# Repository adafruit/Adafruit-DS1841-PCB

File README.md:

## Adafruit DS1841 I2C Logarithmic Potentiometer PCB

<a href="http://www.adafruit.com/products/4570"><br/>
Click here to purchase one from the Adafruit shop</a>

PCB files for the Adafruit DS1841 I2C Logarithmic Potentiometer. 

Format is EagleCAD schematic and board layout
* https://www.adafruit.com/product/4570

### Description

INSERT PRODUCT COPY HERE

### License

Adafruit invests time and resources providing this open source design, please support Adafruit and open-source hardware by purchasing products from [Adafruit](https://www.adafruit.com)!

Designed by Limor Fried for Adafruit Industries.

Creative Commons Attribution/Share-Alike, all text above must be included in any redistribution. 
See license.txt for additional details.

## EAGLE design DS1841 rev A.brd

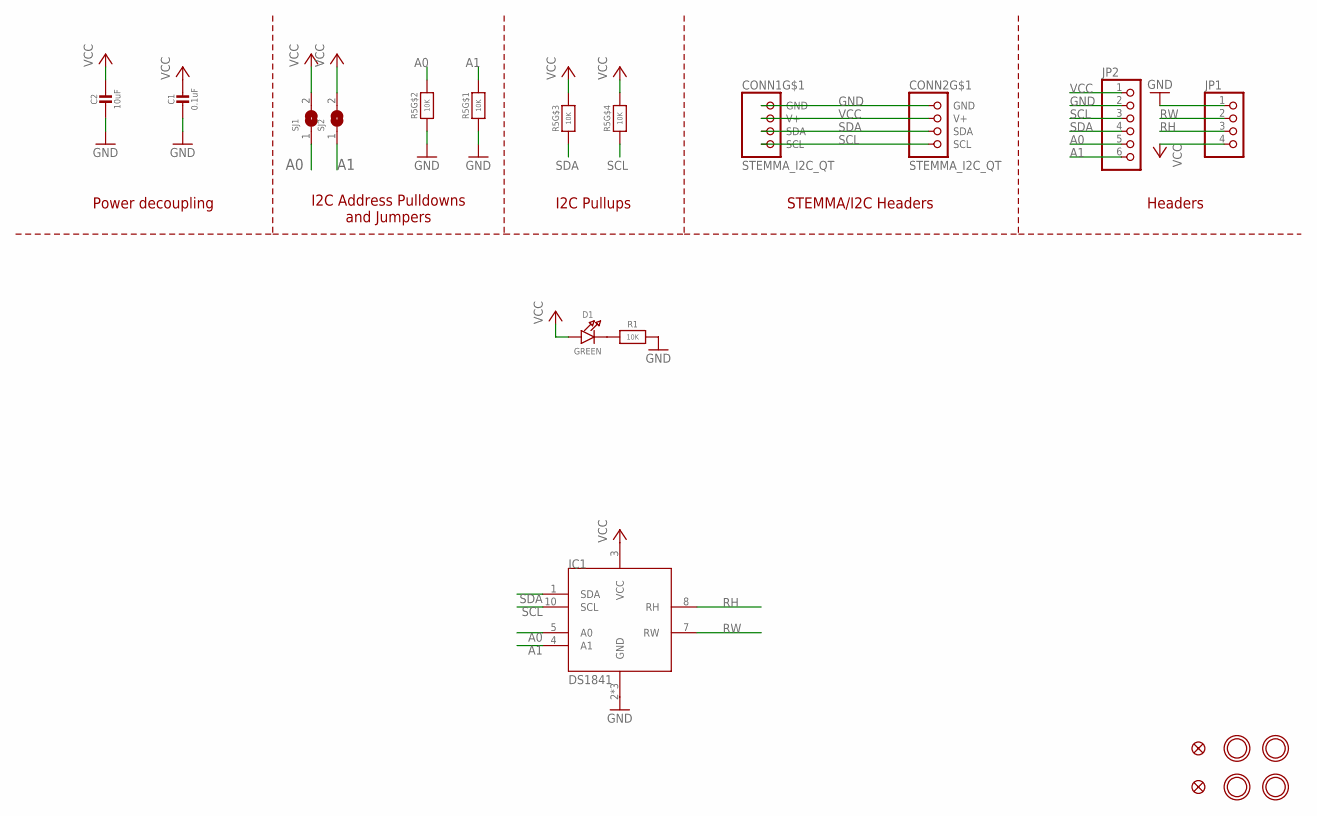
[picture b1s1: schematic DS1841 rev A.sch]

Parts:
C1: 0.1uF; 0603-NO
C2: 10uF; 0805-NO
CONN1, CONN2: STEMMA_I2C_QT; JST_SH4
D1: GREEN; CHIPLED_0603_NOOUTLINE
FID1, FID2: FIDUCIAL_1MM
IC1: DS1841; DFN10_3X3MM
JP1: HEADER-1X4ROUND; 1X04_ROUND
JP2: HEADER-1X6ROUND; 1X06_ROUND
R1: 10K; 0603-NO
R5: 10K; RESPACK_4X0603
SJ1, SJ2: SOLDERJUMPER; SOLDERJUMPER_ARROW_NOPASTE
U$2, U$3, U$6, U$7: MOUNTINGHOLE2.5; MOUNTINGHOLE_2.5_PLATED

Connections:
A0: IC1.5 (A0), JP2.5, R5.7 (2), SJ1.1
A1: IC1.4 (A1), JP2.6, R5.8 (2), SJ2.1
GND: C1.2, C2.2, CONN1.1 (GND), CONN2.1 (GND), IC1.2 (GND), IC1.6 (GND), IC1.GND, JP1.1, JP2.2, R1.2, R5.1, R5.2 (1)
unnamed: D1.C, R1.1
RH: IC1.8 (RH), JP1.3
RW: IC1.7 (RW), JP1.2
SCL: CONN1.4 (SCL), CONN2.4 (SCL), IC1.10 (SCL), JP2.3, R5.4 (1)
SDA: CONN1.3 (SDA), CONN2.3 (SDA), IC1.1 (SDA), JP2.4, R5.3 (1)
VCC: C1.1, C2.1, CONN1.2 (V+), CONN2.2 (V+), D1.A, IC1.3 (VCC), JP1.4, JP2.1, R5.5 (2), R5.6 (2), SJ1.2, SJ2.2

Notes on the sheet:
I2C Address Pulldowns and Jumpers
Power decoupling
I2C Pullups
STEMMA/I2C Headers
Headers

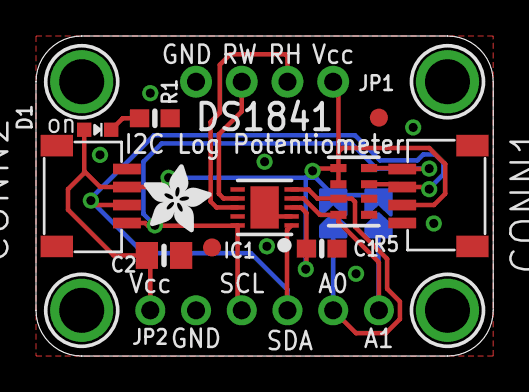
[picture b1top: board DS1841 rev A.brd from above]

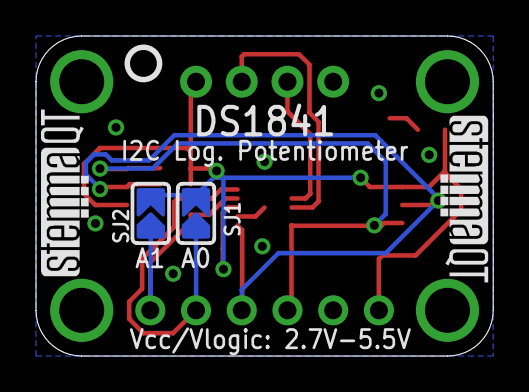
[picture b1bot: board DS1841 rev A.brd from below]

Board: 2 copper layers, 25.4 x 17.8 mm, 22 parts (5 on the bottom side), 9 nets.

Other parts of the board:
U$8: ADAFRUIT_3.5MM
U$9: PCBFEAT-REV-040
U$10, U$11: STEMMAQT

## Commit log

2020-03-24 initial commit; boards not final

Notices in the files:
parts and their libraries:
microbuilder: This work is placed in the public domain, and may be freely used for commercial and non-commercial work with the following conditions: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
